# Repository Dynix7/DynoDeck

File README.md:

# DynoDeck
I plan to design and create a Meshtastic device  that features an E-ink display along with a keyboard.

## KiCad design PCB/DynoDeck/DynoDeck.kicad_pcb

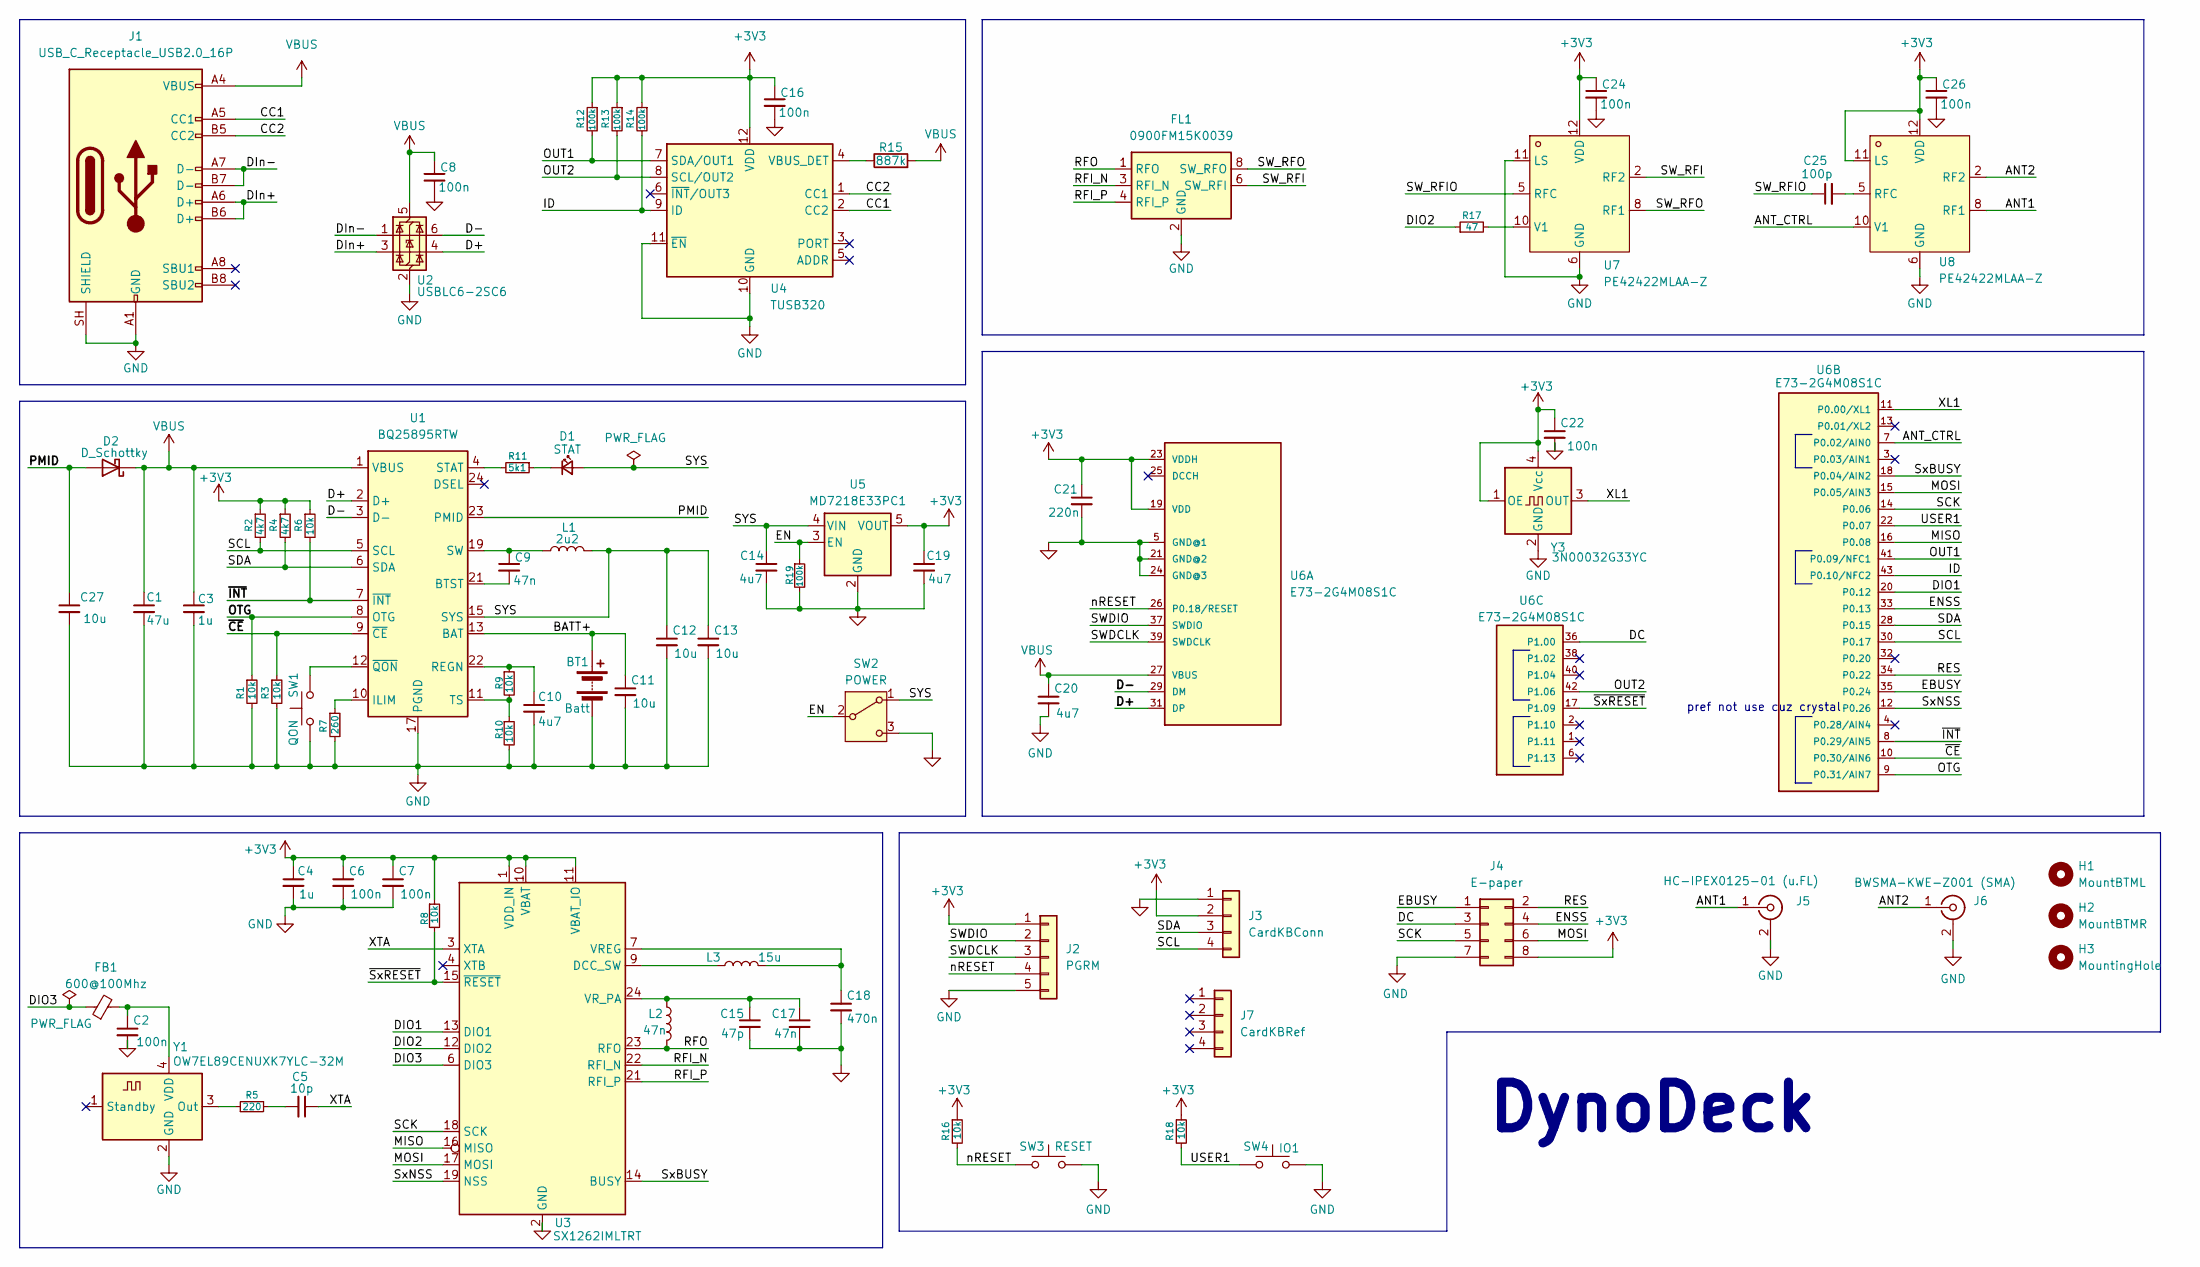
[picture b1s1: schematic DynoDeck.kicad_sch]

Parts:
BT1: Batt; JST_PH_S2B-PH-K_1x02_P2.00mm_Horizontal
C1: 47u; C_0603_1608Metric
C2, C6, C7, C8, C16, C22: 100n; C_0603_1608Metric
C3, C4: 1u; C_0603_1608Metric
C5: 10p; C_0603_1608Metric
C9, C17: 47n; C_0603_1608Metric
C10, C14, C19, C20: 4u7; C_0603_1608Metric
C11, C12, C13, C27: 10u; C_0603_1608Metric
C15: 47p; C_0603_1608Metric
C18: 470n; C_0603_1608Metric
C21: 220n; C_0603_1608Metric
C24, C26: 100n; C_0402_1005Metric
C25: 100p; C_0402_1005Metric
D1: STAT; LED_0603_1608Metric
D2: D_Schottky; D_SMB
FB1: 600@100Mhz; L_0603_1608Metric
FL1: 0900FM15K0039; Balun_Johanson_0900FM15K0039
H1: MountBTML; MountingHole_2.7mm_M2.5
H2: MountBTMR; MountingHole_2.7mm_M2.5
H3: MountingHole; MountingHole_2.7mm_M2.5
J1: USB_C_Receptacle_USB2.0_16P; USB_C_Receptacle_G-Switch_GT-USB-7010ASV
J2: PGRM; PogoPin_1x05_P2.54mm_Pad1.8mm
J3: CardKBConn; JST_PH_S4B-PH-K_1x04_P2.00mm_Horizontal
J4: E-paper; weact_epaper_29
J5: HC-IPEX0125-01 (u.FL); U.FL_Molex_MCRF_73412-0110_Vertical
J6: BWSMA-KWE-Z001 (SMA); SMA_BAT_Wireless_BWSMA-KWE-Z001
J7: CardKBRef
L1: 2u2; L_Sunlord_MWSA0503S
L2: 47n; L_0402_1005Metric
L3: 15u; L_Sunlord_MWSA0503S
R1, R3, R6, R8, R9, R10, R16, R18: 10k; R_0603_1608Metric
R2, R4: 4k7; R_0603_1608Metric
R5: 220; R_0603_1608Metric
R7: 260; R_0603_1608Metric
R11: 5k1; R_0603_1608Metric
R12, R13, R14, R19: 100k; R_0603_1608Metric
R15: 887k; R_0603_1608Metric
R17: 47; R_0603_1608Metric
SW1: QON; SW_SPST_TS-1088-xR020
SW2: POWER; SW_SPDT_CK_JS102011SAQN
SW3: RESET; SW_SPST_TS-1088-xR020
SW4: IO1; SW_SPST_PTS647_Sx38
U1: BQ25895RTW; Texas_RTW_WQFN-24-1EP_4x4mm_P0.5mm_EP2.7x2.7mm_ThermalVias
U2: USBLC6-2SC6; SOT-23-6
U3: SX1262IMLTRT; QFN-24-1EP_4x4mm_P0.5mm_EP2.6x2.6mm
U4: TUSB320; Texas_X2QFN-12_1.6x1.6mm_P0.4mm
U5: MD7218E33PC1; SOT-89-5
U6: E73-2G4M08S1C
U7, U8: PE42422MLAA-Z; PE42422-QFN-12_L2.0-W2.0-P0.50-BL-EP; MPN PE42422MLAA-Z; LCSC Part C500477
Y1: OW7EL89CENUXK7YLC-32M; Oscillator_SMD_Abracon_ASDMB-4Pin_2.5x2.0mm
Y3: 3N00032G33YC; Oscillator_SMD_Abracon_ASE-4Pin_3.2x2.5mm_HandSoldering

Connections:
+3V3: C4.1, C6.1, C7.1, C16.1, C19.1, C21.1, C22.1, C24.1, C26.1, J2.1, J3.2, J4.8, R2.1, R4.1, R6.1, R8.1, R12.1, R13.1, R14.1, R16.1, R18.1, U3.1 (VDD_IN), U3.10 (VBAT), U3.11 (VBAT_IO), U4.12 (VDD), U5.5 (VOUT), U6.19 (VDD), U6.23 (VDDH), U7.12 (VDD), U8.11 (LS), U8.12 (VDD), Y3.1 (OE), Y3.4 (Vcc)
/ANT1: J5.1 (In), U8.8 (RF1)
/ANT2: J6.1 (In), U8.2 (RF2)
/ANT_CTRL: U6.7 (P0.02/AIN0), U8.10 (V1)
/BATT+: BT1.1 (+), C11.1, U1.13 (BAT), U1.14 (BAT)
/CC1: J1.A5 (CC1), U4.2 (CC2)
/CC2: J1.B5 (CC2), U4.1 (CC1)
/D+: U1.2 (D+), U2.4 (I/O2), U6.31 (DP)
/D-: U1.3 (D-), U2.6 (I/O1), U6.29 (DM)
/DC: J4.3, U6.36 (P1.00)
/DIO1: U3.13 (DIO1), U6.20 (P0.12)
/DIO2: R17.1, U3.12 (DIO2)
/DIO3: FB1.1, U3.6 (DIO3)
/DIn+: J1.A6 (D+), J1.B6 (D+), U2.3 (I/O2)
/DIn-: J1.A7 (D-), J1.B7 (D-), U2.1 (I/O1)
/EBUSY: J4.1, U6.35 (P0.24)
/EN: R19.1, SW2.2 (B), U5.3 (EN)
/ENSS: J4.4, U6.33 (P0.13)
/ID: R14.2, U4.9 (ID), U6.43 (P0.10/NFC2)
/MISO: U3.16 (MISO), U6.16 (P0.08)
/MOSI: J4.6, U3.17 (MOSI), U6.15 (P0.05/AIN3)
/OTG: R1.1, U1.8 (OTG), U6.9 (P0.31/AIN7)
/OUT1: R12.2, U4.7 (SDA/OUT1), U6.41 (P0.09/NFC1)
/OUT2: R13.2, U4.8 (SCL/OUT2), U6.42 (P1.06)
/PMID: C27.1, D2.2 (A), U1.23 (PMID)
/RES: J4.2, U6.34 (P0.22)
/RFI_N: FL1.3 (RFI_N), U3.22 (RFI_N)
/RFI_P: FL1.4 (RFI_P), U3.21 (RFI_P)
/RFO: FL1.1 (RFO), L2.1, U3.23 (RFO)
/SCK: J4.5, U3.18 (SCK), U6.14 (P0.06)
/SCL: J3.4, R2.2, U1.5 (SCL), U6.30 (P0.17)
/SDA: J3.3, R4.2, U1.6 (SDA), U6.28 (P0.15)
/SWDCLK: J2.3, U6.39 (SWDCLK)
/SWDIO: J2.2, U6.37 (SWDIO)
/SW_RFI: FL1.6 (SW_RFI), U7.2 (RF2)
/SW_RFIO: C25.1, U7.5 (RFC)
/SW_RFO: FL1.8 (SW_RFO), U7.8 (RF1)
/SYS: C12.1, C13.1, C14.1, D1.2 (A), L1.2, SW2.1 (A), U1.15 (SYS), U1.16 (SYS), U5.4 (VIN)
/SxBUSY: U3.14 (BUSY), U6.18 (P0.04/AIN2)
/SxNSS: U3.19 (NSS), U6.12 (P0.26)
/USER1: R18.2, SW4.1, U6.22 (P0.07)
/XL1: U6.11 (P0.00/XL1), Y3.3 (OUT)
/XTA: C5.1, U3.3 (XTA)
/nRESET: J2.4, R16.2, SW3.1, U6.26 (P0.18/RESET)
/~CE: R3.1, U1.9 (~CE), U6.10 (P0.30/AIN6)
/~INT: R6.2, U1.7 (~INT), U6.8 (P0.29/AIN5)
/~SxRESET: R8.2, U3.15 (~RESET), U6.17 (P1.09)
GND: BT1.2 (-), C1.2, C2.2, C3.2, C4.2, C6.2, C7.2, C8.2, C10.2, C11.2, C12.2, C13.2, C14.2, C15.2, C16.2, C17.2, C18.2, C19.2, C20.2, C21.2, C22.2, C24.2, C26.2, C27.2, FL1.2 (GND), FL1.5 (GND), FL1.7 (GND), FL1.9 (GND), FL1.10 (GND), J1.A1 (GND), J1.A12 (GND), J1.B1 (GND), J1.B12 (GND), J1.SH (SHIELD), J2.5, J3.1, J4.7, J5.2 (Ext), J6.2 (Ext), R1.2, R3.2, R7.2, R10.2, R19.2, SW1.2, SW2.3 (C), SW3.2, SW4.2, U1.17 (PGND), U1.18 (PGND), U1.25 (PGND), U2.2 (GND), U3.2 (GND), U3.5 (GND), U3.8 (GND), U3.20 (GND), U3.25 (GND), U4.10 (GND), U4.11 (~EN), U5.2 (GND), U6.5 (GND@1), U6.21 (GND@2), U6.24 (GND@3), U7.1 (GND), U7.3 (GND), U7.4 (GND/NC), U7.6 (GND), U7.7 (GND), U7.9 (DGND), U7.11 (LS), U7.13 (EP), U8.1 (GND), U8.3 (GND), U8.4 (GND/NC), U8.6 (GND), U8.7 (GND), U8.9 (DGND), U8.13 (EP), Y1.2 (GND), Y3.2 (GND)
unnamed: C5.2, R5.2
unnamed: C9.1, L1.1, U1.19 (SW), U1.20 (SW)
unnamed: D1.1 (K), R11.1
unnamed: C9.2, U1.21 (BTST)
unnamed: R7.1, U1.10 (ILIM)
unnamed: C10.1, R9.1, U1.22 (REGN)
unnamed: R11.2, U1.4 (STAT)
unnamed: R9.2, R10.1, U1.11 (TS)
unnamed: SW1.1, U1.12 (~QON)
unnamed: L3.1, U3.9 (DCC_SW)
unnamed: C18.1, L3.2, U3.7 (VREG)
unnamed: C15.1, C17.1, L2.2, U3.24 (VR_PA)
unnamed: R15.1, U4.4 (VBUS_DET)
unnamed: R17.2, U7.10 (V1)
unnamed: C25.2, U8.5 (RFC)
unnamed: R5.1, Y1.3 (Out)
unnamed: C2.1, FB1.2, Y1.4 (VDD)
VBUS: C1.1, C3.1, C8.1, C20.1, D2.1 (K), J1.A4 (VBUS), J1.A9 (VBUS), J1.B4 (VBUS), J1.B9 (VBUS), R15.2, U1.1 (VBUS), U2.5 (VBUS), U6.27 (VBUS)

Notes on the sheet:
pref not use cuz crystal
DynoDeck

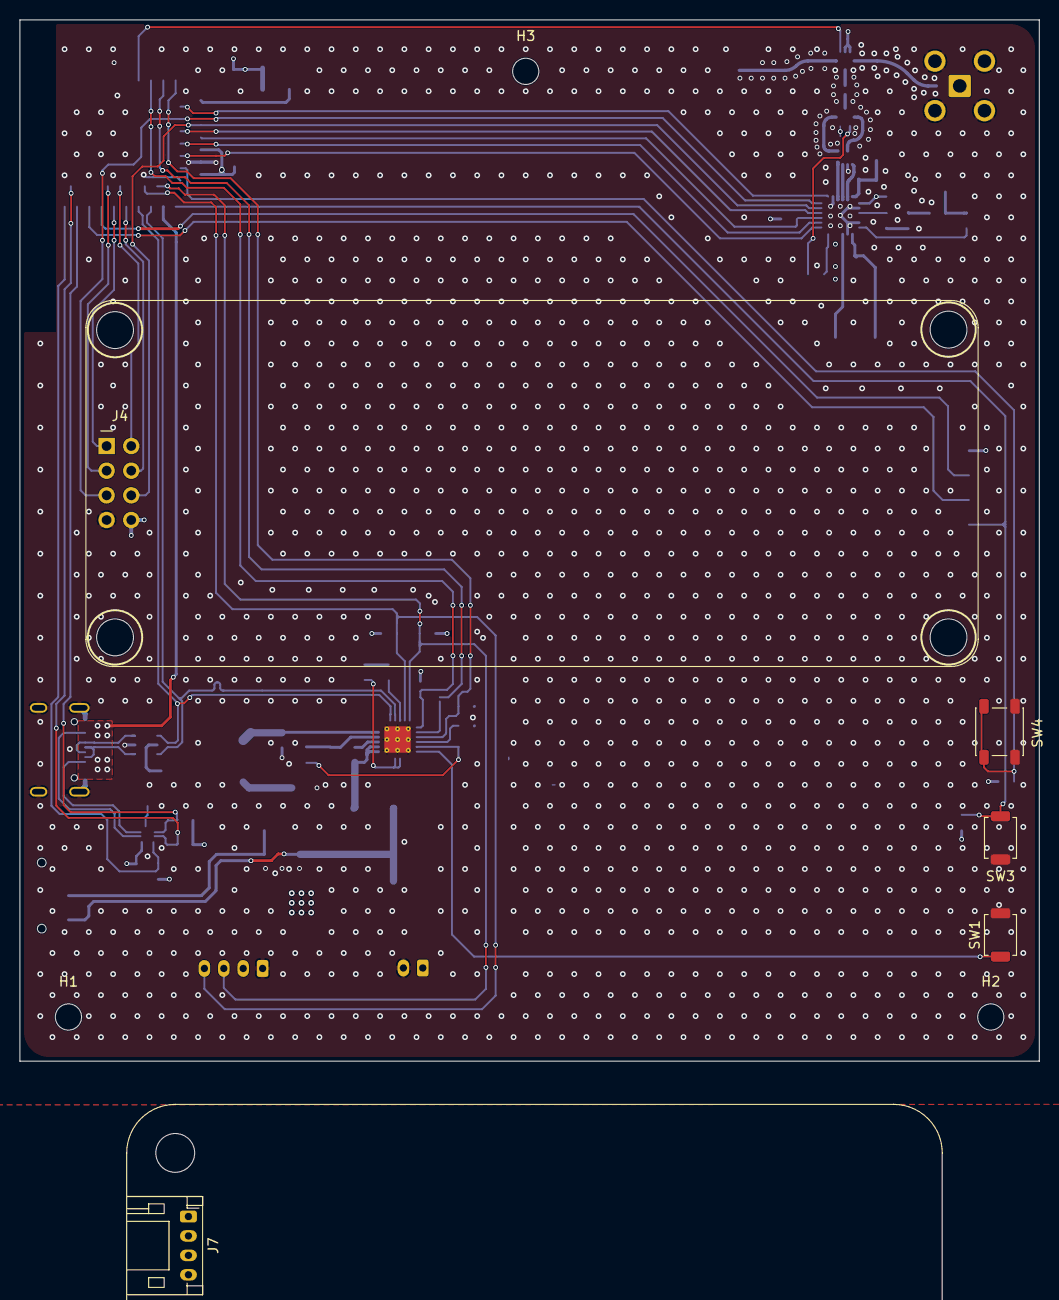
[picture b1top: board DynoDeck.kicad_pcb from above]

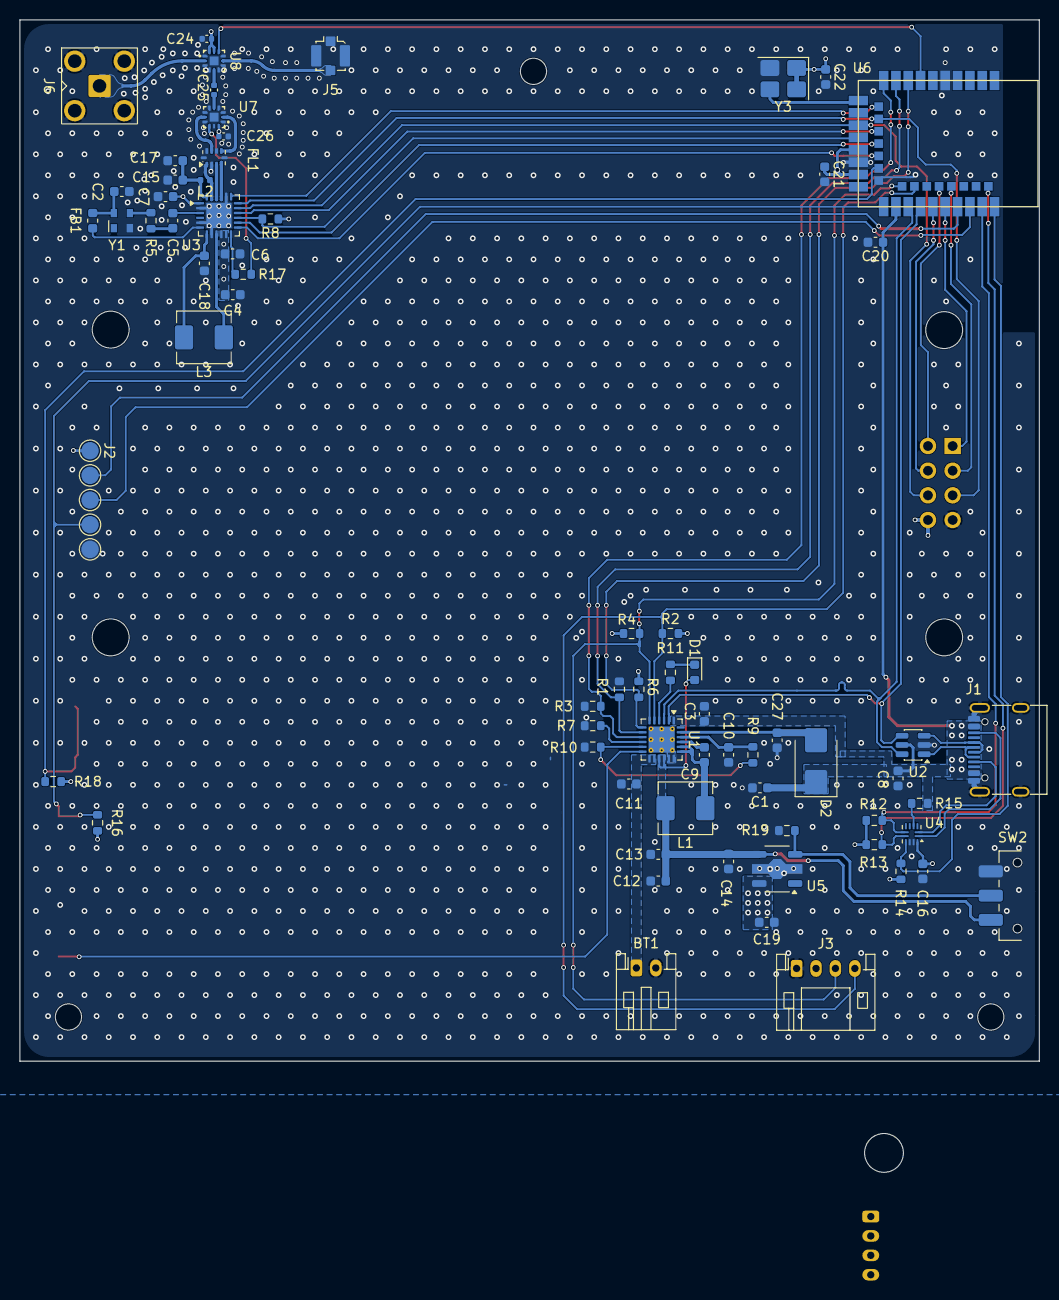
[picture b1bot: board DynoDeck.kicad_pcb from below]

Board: 4 copper layers, 105.0 x 107.3 mm, 77 parts (69 on the bottom side), 66 nets.
